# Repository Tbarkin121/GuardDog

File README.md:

# GuardDog
Makeing a hypoallergenic robot quadruped pet from scratch

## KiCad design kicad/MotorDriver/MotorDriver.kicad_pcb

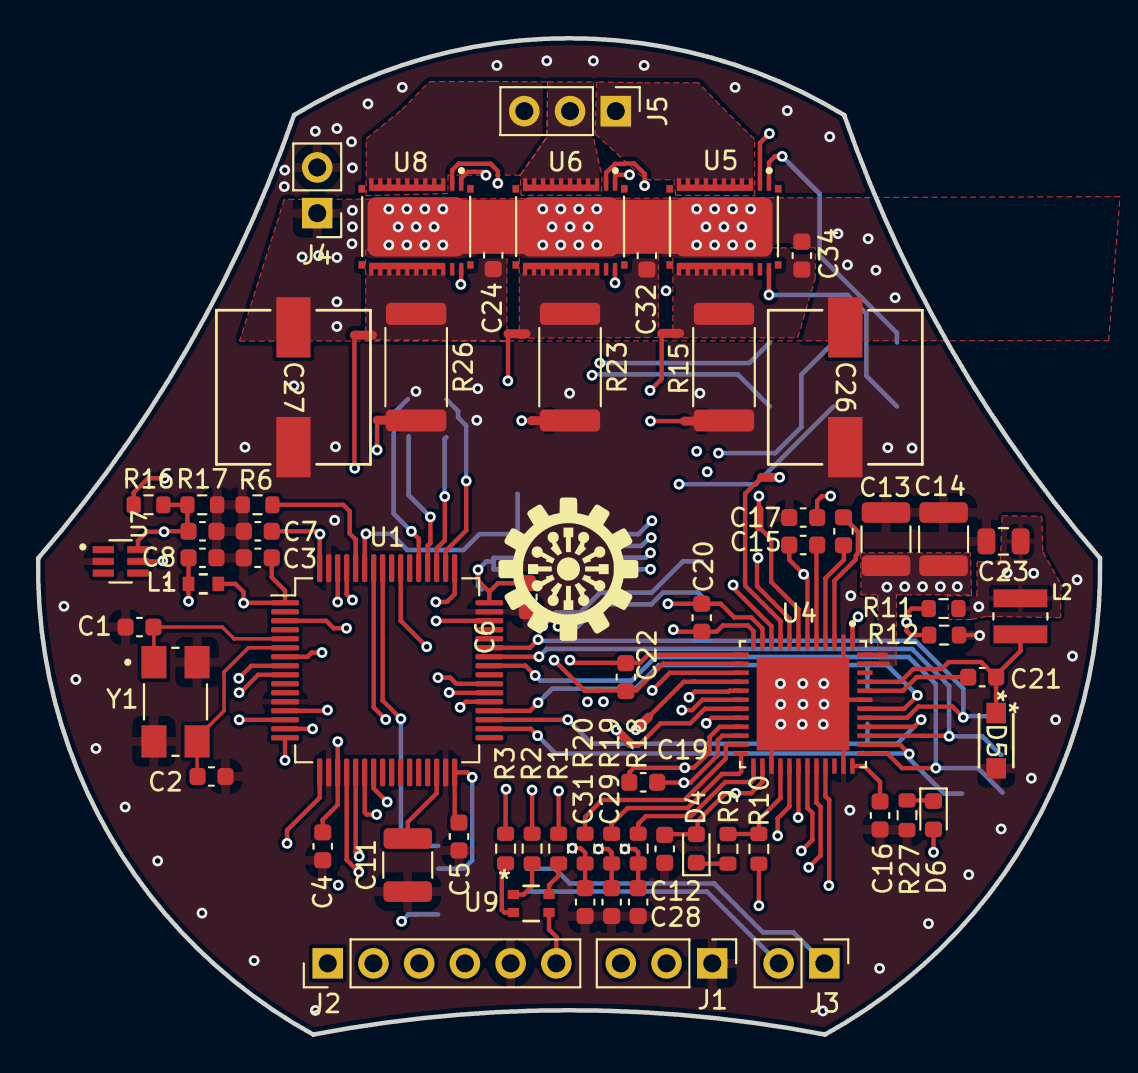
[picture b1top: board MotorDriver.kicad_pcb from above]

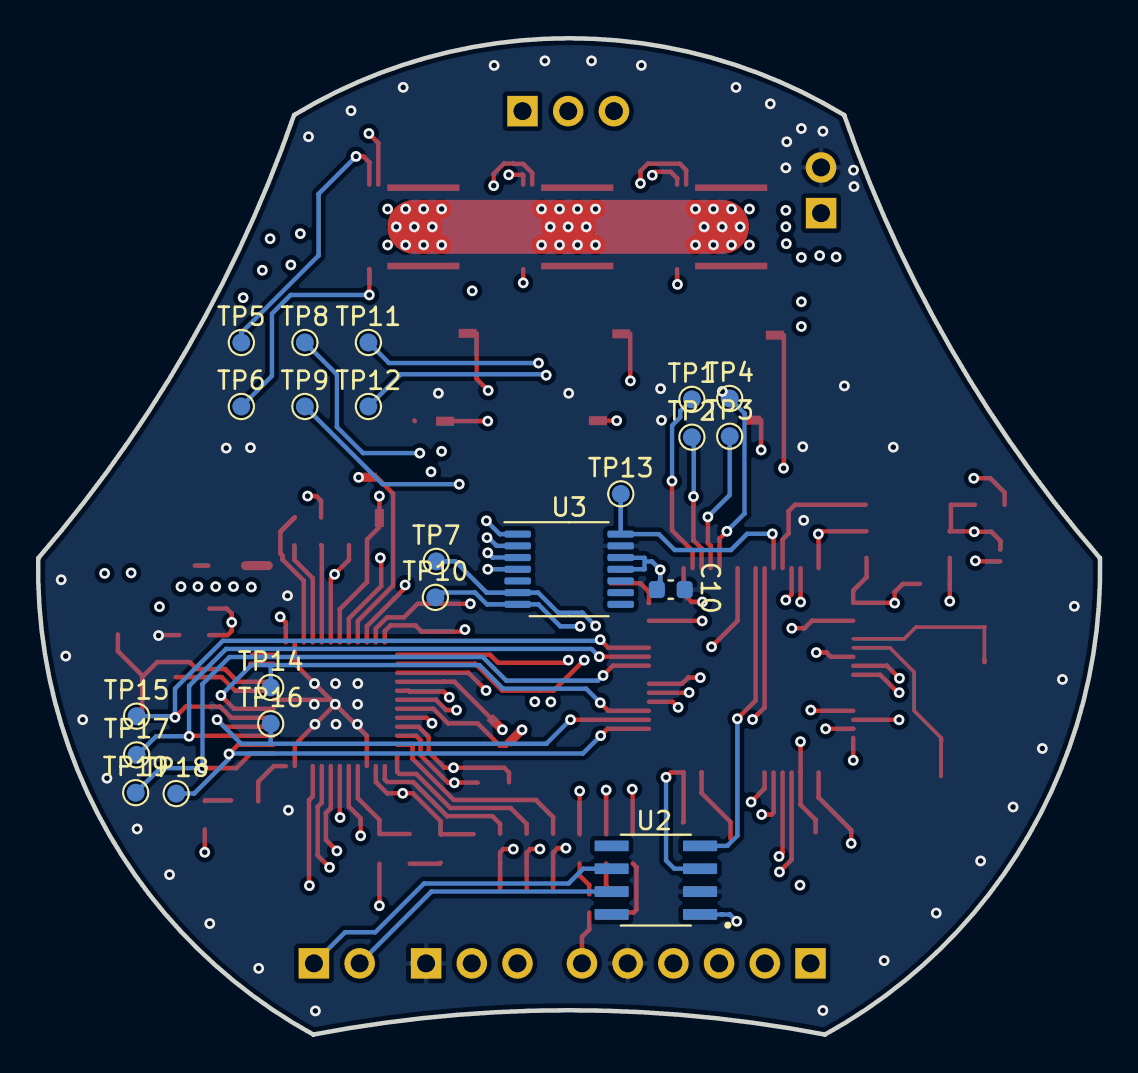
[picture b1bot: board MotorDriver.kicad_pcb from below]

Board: 4 copper layers, 59.0 x 55.3 mm, 97 parts (22 on the bottom side), 84 nets.

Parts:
C1, C2: 18pF; C_0603_1608Metric
C3, C4, C5, C6, C7, C8, C10, C12, C15, C21, C30: 0.1uF; C_0603_1608Metric
C11, C13: 4.7uF; C_1210_3225Metric
C14: 2.2uF; C_1210_3225Metric
C16, C17: 1uF; C_0603_1608Metric
C18: 0.047uF; C_0603_1608Metric
C19, C20, C22: 1000pF; C_0603_1608Metric
C23: 22uF; C_0805_2012Metric
C24, C34: 10000pF; C_0603_1608Metric
C26, C27: 220uF; CHEMI-HA0
C28, C29, C31: 2200pF; C_0603_1608Metric
C32: 10000 pF; C_0603_1608Metric
D4: RedLED; LED_0603_1608Metric
D5: NRVB1H100SFT3G; DIODE_SOD123LF_2P9X1P8_ONS
D6: BlueLED; LED_0603_1608Metric
J1: Conn_01x03_Pin; PinHeader_1x03_P2.54mm_Vertical
J2: Conn_01x06_Pin; PinHeader_1x06_P2.54mm_Vertical
J3: Conn_01x02_Pin; PinHeader_1x02_P2.54mm_Vertical
J4: Conn_01x02_Socket; PinHeader_1x02_P2.54mm_Vertical
J5: Conn_01x03_Socket; PinHeader_1x03_P2.54mm_Vertical
L1: MMZ1608B601CTAH0; IND_1608_TDK
L2: 15uH; IND_VLS3015CX-150M-1
NT1, NT2, NT3, NT4, NT5, NT6, NT7, NT8, NT9, NT10: NetTie_2; NetTie-2_SMD_Pad0.5mm
R1, R9, R27: 330; R_0603_1608Metric
R2, R3: 1k; R_0603_1608Metric
R6, R10: 10k; R_0603_1608Metric
R11: 28.0k; R_0603_1608Metric
R12: 8.45k; R_0603_1608Metric
R15, R23, R26: 0.007; R_2512_6332Metric
R16: 82.0k; R_0603_1608Metric
R17: 4.99k; R_0603_1608Metric
R18, R19, R20: 56; R_0603_1608Metric
TP1, TP2, TP3, TP4, TP5, TP6, TP7, TP8, TP9, TP10, TP11, TP12, TP13, TP14, TP15, TP16, TP17, TP18, TP19: TestPoint; TestPoint_Pad_D1.0mm
U1: STM32F446RETx; LQFP-64_10x10mm_P0.5mm
U2: ATA6560-GAQW; SOIC127P600X175-8N
U3: AS5147U; TSSOP-14_4.4x5mm_P0.65mm
U4: DRV8323RSRGZR; QFN50P700X700X100-49N
U5, U6, U8: CSD88599Q5DC; MOSFET_CSD88599Q5DC
U7: TPD4S009DCKR; SOT65P210X110-6N
U9: 150066M153000; CHIP_M153000_WRE
Y1: 406I35D08M00000; XTAL_406I35D08M00000

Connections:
+3.3V: C3.2, C4.2, C5.2, C6.2, C7.2, C10.2, C12.1, C23.1, D4.2 (A), D6.2 (A), J2.6, L1.2, L2.2, R10.1, R11.1, U1.1 (VBAT), U1.19 (VDD), U1.32 (VDD), U1.48 (VDD), U1.64 (VDD), U2.3 (VCC), U3.11 (VDD), U3.12 (3V3), U4.26 (VREF), U7.5 (VCC), U9.4
/Encoder/M1_ENC.A: TP10.1, U1.61 (PB8), U3.7 (A)
/Encoder/M1_ENC.B: TP7.1, U1.62 (PB9), U3.6 (B)
/Encoder/M1_ENC.I: TP13.1, U1.59 (PB7), U3.14 (I/PWM)
/Encoder/SPI3.CS: TP1.1, U1.50 (PA15), U3.1 (CSn)
/Encoder/SPI3.MISO: TP3.1, U1.52 (PC11), U3.3 (MISO)
/Encoder/SPI3.MOSI: TP4.1, U1.53 (PC12), U3.4 (MOSI)
/Encoder/SPI3.SCK: TP2.1, U1.51 (PC10), U3.2 (CLK)
/Microcontroller/BOOT0: R6.1, U1.60 (BOOT0)
/Microcontroller/CAN2_RX: U1.57 (PB5), U2.4 (RXD)
/Microcontroller/CAN2_TX: U1.58 (PB6), U2.1 (TXD)
/Microcontroller/CLK_N: C2.2, U1.6 (PH1), Y1.3
/Microcontroller/CLK_P: C1.2, U1.5 (PH0), Y1.1
/Microcontroller/DRV.ENABLE: U1.3 (PC14), U4.33 (ENABLE)
/Microcontroller/DRV.INHA: TP19.1, U1.41 (PA8), U4.37 (INHA)
/Microcontroller/DRV.INHB: TP17.1, U1.42 (PA9), U4.39 (INHB)
/Microcontroller/DRV.INHC: TP15.1, U1.43 (PA10), U4.41 (INHC)
/Microcontroller/DRV.INLA: TP18.1, U1.34 (PB13), U4.38 (INLA)
/Microcontroller/DRV.INLB: TP16.1, U1.35 (PB14), U4.40 (INLB)
/Microcontroller/DRV.INLC: TP14.1, U1.36 (PB15), U4.42 (INLC)
/Microcontroller/NRST: J2.1, U1.7 (NRST)
/Microcontroller/SEN.ISENA: C28.1, R18.2, U1.14 (PA0)
/Microcontroller/SEN.ISENB: C29.1, R19.2, U1.9 (PC1)
/Microcontroller/SEN.ISENC: C31.1, R20.2, U1.8 (PC0)
/Microcontroller/SEN.VSENVM: C30.1, R16.2, R17.1, U1.15 (PA1), U7.6 (D1-)
/Microcontroller/SPI1.CS: U1.20 (PA4), U4.32 (SCS_N)
/Microcontroller/SPI1.MISO: U1.22 (PA6), U4.29 (SDO)
/Microcontroller/SPI1.MOSI: U1.23 (PA7), U4.30 (SDI)
/Microcontroller/SPI1.SCK: U1.21 (PA5), U4.31 (SCLK)
/Microcontroller/SWO: J2.4, U1.55 (PB3)
/Microcontroller/TCK: J2.2, U1.49 (PA14)
/Microcontroller/TMS: J2.3, U1.46 (PA13)
/Microcontroller/UART_RX: J1.2, U1.17 (PA3)
/Microcontroller/UART_TX: J1.3, U1.16 (PA2)
/Microcontroller/VDDA: C8.2, L1.1, U1.13 (VDDA)
/MotorController/GHA: TP5.1, U4.8 (GHA), U5.1 (GH)
/MotorController/GHB: TP8.1, U4.17 (GHB), U6.1 (GH)
/MotorController/GHC: TP11.1, U4.18 (GHC), U8.1 (GH)
/MotorController/GLA: TP6.1, U4.10 (GLA), U5.22 (GL)
/MotorController/GLB: TP9.1, U4.15 (GLB), U6.22 (GL)
/MotorController/GLC: TP12.1, U4.20 (GLC), U8.22 (GL)
/MotorController/MOTA: J5.1, U5.3 (VSW), U5.4 (VSW), U5.5 (VSW), U5.6 (VSW), U5.7 (VSW), U5.8 (VSW), U5.9 (VSW), U5.10 (VSW), U5.11 (VSW)
/MotorController/MOTB: J5.2, U6.3 (VSW), U6.4 (VSW), U6.5 (VSW), U6.6 (VSW), U6.7 (VSW), U6.8 (VSW), U6.9 (VSW), U6.10 (VSW), U6.11 (VSW)
/MotorController/MOTC: J5.3, U8.3 (VSW), U8.4 (VSW), U8.5 (VSW), U8.6 (VSW), U8.7 (VSW), U8.8 (VSW), U8.9 (VSW), U8.10 (VSW), U8.11 (VSW)
/MotorController/SHA: NT3.2, U4.9 (SHA)
/MotorController/SHB: NT7.2, U4.16 (SHB)
/MotorController/SHC: NT10.2, U4.19 (SHC)
/MotorController/SLA: C24.2, NT1.2, R15.1, U5.12 (PGND), U5.13 (PGND), U5.14 (PGND), U5.15 (PGND), U5.16 (PGND), U5.17 (PGND), U5.18 (PGND), U5.19 (PGND), U5.20 (PGND)
/MotorController/SLB: C32.2, NT5.2, R23.1, U6.12 (PGND), U6.13 (PGND), U6.14 (PGND), U6.15 (PGND), U6.16 (PGND), U6.17 (PGND), U6.18 (PGND), U6.19 (PGND), U6.20 (PGND)
/MotorController/SLC: C34.2, NT8.2, R26.1, U8.12 (PGND), U8.13 (PGND), U8.14 (PGND), U8.15 (PGND), U8.16 (PGND), U8.17 (PGND), U8.18 (PGND), U8.19 (PGND), U8.20 (PGND)
/MotorController/SNA: C20.2, NT2.1, U4.12 (SNA)
/MotorController/SNB: C22.2, NT6.1, U4.13 (SNB)
/MotorController/SNC: C19.2, NT9.1, U4.22 (SNC)
/MotorController/SOA: R18.1, U4.25 (SOA)
/MotorController/SOB: R19.1, U4.24 (SOB)
/MotorController/SOC: R20.1, U4.23 (SOC)
/MotorController/SPA: C20.1, NT1.1, U4.11 (SPA)
/MotorController/SPB: C22.1, NT5.1, U4.14 (SPB)
/MotorController/SPC: C19.1, NT8.1, U4.21 (SPC)
/MotorController/VDRAIN: NT4.1, U4.7 (VDRAIN)
/MotorController/nFault: R9.2, R10.2, U4.28 (FAULT_N)
GND: C1.1, C2.1, C3.1, C4.1, C5.1, C6.1, C7.1, C8.1, C10.1, C11.1, C12.2, C13.2, C14.2, C15.2, C16.2, C23.2, C26.2, C27.2, C28.2, C29.2, C30.2, C31.2, D5.2 (A), J1.1, J2.5, J4.2, NT2.2, NT6.2, NT9.2, R6.2, R12.2, R15.2, R17.2, R23.2, R26.2, R27.2, U1.12 (VSSA), U1.18 (VSS), U1.31 (VSS), U1.47 (VSS), U1.63 (VSS), U2.2 (GND), U3.13 (GND), U4.2 (PGND), U4.27 (DGND), U4.35 (AGND), U4.43 (BGND), U4.49 (EP), U7.2 (GND), Y1.2 (GND), Y1.4 (GND__1)
unnamed: D4.1 (K), R9.1
unnamed: C21.2, D5.1 (K), L2.1, U4.45 (SW)
unnamed: D6.1 (K), R27.1
unnamed: J3.1, U2.6 (CANL)
unnamed: J3.2, U2.7 (CANH)
unnamed: R1.2, U9.3
unnamed: R2.2, U9.2
unnamed: R3.2, U9.1
unnamed: R1.1, U1.37 (PC6)
unnamed: R2.1, U1.38 (PC7)
unnamed: R3.1, U1.39 (PC8)
unnamed: C11.2, U1.30 (VCAP_1)
unnamed: C21.1, U4.44 (CB)
unnamed: C18.1, U4.4 (CPH)
unnamed: C18.2, U4.3 (CPL)
unnamed: C16.1, U4.36 (DVDD)
unnamed: R11.2, R12.1, U4.1 (FB)
unnamed: C17.2, U4.5 (VCP)
unnamed: NT3.1, U5.2 (SH)
unnamed: NT7.1, U6.2 (SH)
unnamed: NT10.1, U8.2 (SH)
Vdrive: C13.1, C14.1, C15.1, C17.1, C24.1, C26.1, C27.1, C32.1, C34.1, J4.1, NT4.2, R16.1, U4.6 (VM), U4.47 (VIN), U4.48 (SHDN_N), U5.27 (VIN), U6.27 (VIN), U8.27 (VIN)

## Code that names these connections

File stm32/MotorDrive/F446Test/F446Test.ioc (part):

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Mcu.Name=STM32F446R(C-E)Tx
Mcu.Package=LQFP64
Mcu.UserName=STM32F446RETx
PA0-WKUP.GPIOParameters=GPIO_Label
PA0-WKUP.GPIO_Label=M1_CURR_AMPL_U
PA0-WKUP.Signal=ADCx_IN0
PA1.GPIOParameters=GPIO_Label
PA1.GPIO_Label=M1_BUS_VOLTAGE
PA1.Signal=ADCx_IN1
PA10.GPIOParameters=GPIO_Speed,GPIO_PuPd,GPIO_Label
PA10.GPIO_Label=M1_PWM_WH
PA10.GPIO_PuPd=GPIO_PULLDOWN
PA10.GPIO_Speed=GPIO_SPEED_FREQ_HIGH
PA10.Signal=S_TIM1_CH3
PA13.Mode=Trace_Asynchronous_SW
PA13.Signal=SYS_JTMS-SWDIO
PA14.Mode=Trace_Asynchronous_SW
PA14.Signal=SYS_JTCK-SWCLK
PA15.GPIOParameters=GPIO_Label
PA15.GPIO_Label=SPI3_CS
PA15.Signal=GPIO_Output
PA2.GPIOParameters=GPIO_Speed,GPIO_PuPd,GPIO_Label,GPIO_Mode
PA2.GPIO_Label=UART_TX
PA2.GPIO_Mode=GPIO_MODE_AF_PP
PA2.GPIO_PuPd=GPIO_NOPULL
PA2.GPIO_Speed=GPIO_SPEED_FREQ_LOW
PA2.Mode=Asynchronous
PA2.Signal=USART2_TX
PA3.GPIOParameters=GPIO_Speed,GPIO_PuPd,GPIO_Label,GPIO_Mode
PA3.GPIO_Label=UART_RX
PA3.GPIO_Mode=GPIO_MODE_AF_PP
PA3.GPIO_PuPd=GPIO_NOPULL
PA3.GPIO_Speed=GPIO_SPEED_FREQ_LOW
PA3.Mode=Asynchronous
PA3.Signal=USART2_RX
PA4.GPIOParameters=GPIO_Label
PA4.GPIO_Label=SPI1_CS
PA4.Signal=GPIO_Output
PA5.Mode=Full_Duplex_Master
PA5.Signal=SPI1_SCK
PA6.Mode=Full_Duplex_Master
PA6.Signal=SPI1_MISO
PA7.Mode=Full_Duplex_Master
PA7.Signal=SPI1_MOSI
PA8.GPIOParameters=GPIO_Speed,GPIO_PuPd,GPIO_Label
PA8.GPIO_Label=M1_PWM_UH
PA8.GPIO_PuPd=GPIO_PULLDOWN
PA8.GPIO_Speed=GPIO_SPEED_FREQ_HIGH
PA8.Signal=S_TIM1_CH1
PA9.GPIOParameters=GPIO_Speed,GPIO_PuPd,GPIO_Label
PA9.GPIO_Label=M1_PWM_VH
PA9.GPIO_PuPd=GPIO_PULLDOWN
PA9.GPIO_Speed=GPIO_SPEED_FREQ_HIGH
PA9.Signal=S_TIM1_CH2
PB13.GPIOParameters=GPIO_Speed,GPIO_PuPd,GPIO_Label
PB13.GPIO_Label=M1_PWM_UL
PB13.GPIO_PuPd=GPIO_PULLDOWN
PB13.GPIO_Speed=GPIO_SPEED_FREQ_HIGH
PB13.Mode=PWM Generation1 CH1 CH1N
PB13.Signal=TIM1_CH1N
PB14.GPIOParameters=GPIO_Speed,GPIO_PuPd,GPIO_Label
PB14.GPIO_Label=M1_PWM_VL
PB14.GPIO_PuPd=GPIO_PULLDOWN
PB14.GPIO_Speed=GPIO_SPEED_FREQ_HIGH
PB14.Mode=PWM Generation2 CH2 CH2N
PB14.Signal=TIM1_CH2N
PB15.GPIOParameters=GPIO_Speed,GPIO_PuPd,GPIO_Label
PB15.GPIO_Label=M1_PWM_WL
PB15.GPIO_PuPd=GPIO_PULLDOWN
PB15.GPIO_Speed=GPIO_SPEED_FREQ_HIGH
PB15.Mode=PWM Generation3 CH3 CH3N
PB15.Signal=TIM1_CH3N
PB3.Mode=Trace_Asynchronous_SW
PB3.Signal=SYS_JTDO-SWO
PB5.Mode=CAN_Activate
PB5.Signal=CAN2_RX
PB6.Mode=CAN_Activate
PB6.Signal=CAN2_TX
PB8.GPIOParameters=GPIO_Label
PB8.GPIO_Label=M1_ENCODER_A
PB8.Signal=S_TIM2_CH1_ETR
PB9.GPIOParameters=GPIO_Label
PB9.GPIO_Label=M1_ENCODER_B
PB9.Signal=S_TIM2_CH2
PC0.GPIOParameters=GPIO_Label
PC0.GPIO_Label=M1_CURR_AMPL_W
PC0.Signal=ADCx_IN10
PC1.GPIOParameters=GPIO_Label
PC1.GPIO_Label=M1_CURR_AMPL_V
PC1.Signal=ADCx_IN11
PC10.Mode=Full_Duplex_Master
PC10.Signal=SPI3_SCK
PC11.Mode=Full_Duplex_Master
PC11.Signal=SPI3_MISO
PC12.Mode=Full_Duplex_Master
PC12.Signal=SPI3_MOSI
PC13.GPIOParameters=GPIO_PuPd,GPIO_Label,GPIO_ModeDefaultEXTI
PC13.GPIO_Label=Start/Stop [PushButton]
PC13.GPIO_ModeDefaultEXTI=GPIO_MODE_IT_FALLING
PC13.GPIO_PuPd=GPIO_NOPULL
PC13.Signal=GPXTI13
PC3.Signal=ADCx_IN13
PC4.Signal=ADCx_IN14
PC5.Signal=ADCx_IN15
PH0-OSC_IN.Mode=HSE-External-Oscillator
PH0-OSC_IN.Signal=RCC_OSC_IN
PH1-OSC_OUT.Mode=HSE-External-Oscillator
PH1-OSC_OUT.Signal=RCC_OSC_OUT
RCC.HSE_VALUE=8000000
RCC.SYSCLKFreq_VALUE=180000000
RCC.SYSCLKSource=RCC_SYSCLKSOURCE_PLLCLK
board=custom

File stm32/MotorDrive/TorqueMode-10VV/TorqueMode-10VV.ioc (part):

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Mcu.Name=STM32F446R(C-E)Tx
Mcu.Package=LQFP64
Mcu.UserName=STM32F446RETx
PA0-WKUP.GPIOParameters=GPIO_Label
PA0-WKUP.GPIO_Label=M1_CURR_AMPL_U
PA0-WKUP.Signal=ADCx_IN0
PA1.GPIOParameters=GPIO_Label
PA1.GPIO_Label=M1_BUS_VOLTAGE
PA1.Signal=ADCx_IN1
PA10.GPIOParameters=GPIO_Speed,GPIO_PuPd,GPIO_Label
PA10.GPIO_Label=M1_PWM_WH
PA10.GPIO_PuPd=GPIO_PULLDOWN
PA10.GPIO_Speed=GPIO_SPEED_FREQ_HIGH
PA10.Signal=S_TIM1_CH3
PA15.GPIOParameters=GPIO_Speed,GPIO_Label
PA15.GPIO_Label=SPI3_CS
PA15.GPIO_Speed=GPIO_SPEED_FREQ_VERY_HIGH
PA15.Signal=GPIO_Output
PA2.GPIOParameters=GPIO_Speed,GPIO_PuPd,GPIO_Label,GPIO_Mode
PA2.GPIO_Label=UART_TX
PA2.GPIO_Mode=GPIO_MODE_AF_PP
PA2.GPIO_PuPd=GPIO_NOPULL
PA2.GPIO_Speed=GPIO_SPEED_FREQ_LOW
PA2.Mode=Asynchronous
PA2.Signal=USART2_TX
PA3.GPIOParameters=GPIO_Speed,GPIO_PuPd,GPIO_Label,GPIO_Mode
PA3.GPIO_Label=UART_RX
PA3.GPIO_Mode=GPIO_MODE_AF_PP
PA3.GPIO_PuPd=GPIO_NOPULL
PA3.GPIO_Speed=GPIO_SPEED_FREQ_LOW
PA3.Mode=Asynchronous
PA3.Signal=USART2_RX
PA4.GPIOParameters=GPIO_Speed,GPIO_Label
PA4.GPIO_Label=SPI1_CS
PA4.GPIO_Speed=GPIO_SPEED_FREQ_VERY_HIGH
PA4.Signal=GPIO_Output
PA5.Mode=Full_Duplex_Master
PA5.Signal=SPI1_SCK
PA6.GPIOParameters=GPIO_PuPd
PA6.GPIO_PuPd=GPIO_PULLUP
PA6.Mode=Full_Duplex_Master
PA6.Signal=SPI1_MISO
PA7.Mode=Full_Duplex_Master
PA7.Signal=SPI1_MOSI
PA8.GPIOParameters=GPIO_Speed,GPIO_PuPd,GPIO_Label
PA8.GPIO_Label=M1_PWM_UH
PA8.GPIO_PuPd=GPIO_PULLDOWN
PA8.GPIO_Speed=GPIO_SPEED_FREQ_HIGH
PA8.Signal=S_TIM1_CH1
PA9.GPIOParameters=GPIO_Speed,GPIO_PuPd,GPIO_Label
PA9.GPIO_Label=M1_PWM_VH
PA9.GPIO_PuPd=GPIO_PULLDOWN
PA9.GPIO_Speed=GPIO_SPEED_FREQ_HIGH
PA9.Signal=S_TIM1_CH2
PB13.GPIOParameters=GPIO_Speed,GPIO_PuPd,GPIO_Label
PB13.GPIO_Label=M1_PWM_UL
PB13.GPIO_PuPd=GPIO_PULLDOWN
PB13.GPIO_Speed=GPIO_SPEED_FREQ_HIGH
PB13.Mode=PWM Generation1 CH1 CH1N
PB13.Signal=TIM1_CH1N
PB14.GPIOParameters=GPIO_Speed,GPIO_PuPd,GPIO_Label
PB14.GPIO_Label=M1_PWM_VL
PB14.GPIO_PuPd=GPIO_PULLDOWN
PB14.GPIO_Speed=GPIO_SPEED_FREQ_HIGH
PB14.Mode=PWM Generation2 CH2 CH2N
PB14.Signal=TIM1_CH2N
PB15.GPIOParameters=GPIO_Speed,GPIO_PuPd,GPIO_Label
PB15.GPIO_Label=M1_PWM_WL
PB15.GPIO_PuPd=GPIO_PULLDOWN
PB15.GPIO_Speed=GPIO_SPEED_FREQ_HIGH
PB15.Mode=PWM Generation3 CH3 CH3N
PB15.Signal=TIM1_CH3N
PB8.GPIOParameters=GPIO_Label
PB8.GPIO_Label=M1_ENCODER_A
PB8.Signal=S_TIM2_CH1_ETR
PB9.GPIOParameters=GPIO_Label
PB9.GPIO_Label=M1_ENCODER_B
PB9.Signal=S_TIM2_CH2
PC0.GPIOParameters=GPIO_Label
PC0.GPIO_Label=M1_CURR_AMPL_W
PC0.Signal=ADCx_IN10
PC1.GPIOParameters=GPIO_Label
PC1.GPIO_Label=M1_CURR_AMPL_V
PC1.Signal=ADCx_IN11
PC10.Mode=Full_Duplex_Master
PC10.Signal=SPI3_SCK
PC11.GPIOParameters=GPIO_PuPd
PC11.GPIO_PuPd=GPIO_PULLUP
PC11.Mode=Full_Duplex_Master
PC11.Signal=SPI3_MISO
PC12.Mode=Full_Duplex_Master
PC12.Signal=SPI3_MOSI
PC14-OSC32_IN.Signal=GPIO_Output
PC6.Signal=GPIO_Output
PC7.Signal=GPIO_Output
PC8.Signal=GPIO_Output
PH0-OSC_IN.Mode=HSE-External-Oscillator
PH0-OSC_IN.Signal=RCC_OSC_IN
PH1-OSC_OUT.Mode=HSE-External-Oscillator
PH1-OSC_OUT.Signal=RCC_OSC_OUT
RCC.HSE_VALUE=8000000
RCC.SYSCLKFreq_VALUE=180000000
RCC.SYSCLKSource=RCC_SYSCLKSOURCE_PLLCLK
board=custom

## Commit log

2023-11-20 Pushing project files for remote work
2023-11-27 Good progress on the leg prototype. Looking at the jacobian project again, i think I can use some stuff from that project to help size the link lengths and also something to relate the tip forces to 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
2023-11-28 Added urdf for Torque Pole
2023-11-29 Jacobians and pendulum simulation with lagrangian mechanics added
2023-11-29 Added friction and input torque. Did a constant velocity following experiment. Gonna move to multi-joint now... I think this is too simple
2023-11-29 Multisegment is in but I'm not accounting for translational energy, coriolis or centrifugal forces... needs work
2023-11-30 Still working it out...
2023-11-30 The 2 joint force / torque kinematic jacobian looks like its working.
2023-11-30 Just playing with it a bit more. It is starting to become more intuitive
2023-12-02 Just syncing from my macbook
2023-12-04 Schematic capture is like 80% complete. There are some components that don't have appropriate footprints, IE the 330 mH caps. Started board layout. I'm not sure if I can fit everything in the current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
2023-12-05 Pushing before the drive to Boston...
2023-12-12 Updated the planetary gearbox design. It is much better with retaining rings and bearing support. 95% done with the PCB routing. Need to just do a final routing check and i think I can put the order 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
2023-12-13 PCB ordered
2023-12-13 Added a new URDF with 0.5m long connections and a 500g foot piece
2023-12-13 Added some isaac stuff. Started testing the URDF in some simple python code
2023-12-20 Started to test the large bearing build
2024-01-03 Made a new torquepole assembly
2024-01-03 Created a test environment for the new URDF. I want to modify it to add a weight to the end before moving forward
2024-01-03 Added weight to the torque pole
2024-01-03 Second attempt...
2024-01-04 Kind of working, need redefine pendulum neutral state as up though
2024-01-04 Flipped the pole orientation to upward
2024-01-04 Training is working
2024-01-04 Was able to generate an onnx file from the trained pendulum model. Needed to make a modification to rl_games:torch_runner to generate the onnx file during the test playback... trying hardware in the 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
2024-01-04 Got Python to STM32 serial comms up
2024-01-06 Python script is communicating with the STM32. Python script can send two floats for the observation and recieves 4 floats (Value, Mu, Log_STD, InferenceTime). Inference time results in about a 700 H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
2024-01-06 Hardware in the loop control is working from the STM32G431. But can it run anymal terrain?
2024-01-07 Well it can't run anymal terrain due to flash size limitations. But I started looking into external memory so maybe in the future. Anymal (not terrain) runs at 96 Hz though which is pretty impressive
2024-01-14 Got most of the STM32 code together for the inverted pendulum. I just need to double check that the encoder measurements are using the same conventions as isaac
2024-01-15 The NN + Motor driver worked beautifully. Ready for the writeup. Updated URDF again, was thinking of trying some parameter randomization for a more robust policy.
2024-01-15 Updated URDF with the measured mass of the CF-tube and ASA-weight
2024-01-15 Learned a new policy with the current hardware setup, time to test on HW
2024-01-16 Got a better pendulum policy to test on HW
2024-01-16 New policy
2024-01-16 One more try for tonight
2024-01-16 Just noticed I was working out of the old LegDay directory so my changes weren't being pushed... fixed. use the cube_workspace in the future
2024-01-16 Made some models for slightly higher max torques. Also missing some MCsdk files so i cant build the embedded code on linux yet
2024-01-16 Got the stm32 directory organized. There is now one project, LegDay, which contains the torquepole code. I included the missing files that linux might not have been downloading but im not 100% sure i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
2024-02-27 Added some mecanical updates... also this project needs some file organization...
2024-03-11 Solidworks file cleanup... it was a mess!
2024-03-12 Added URDF for jump test
2024-03-12 Got keyboard control of jumpy working.
2024-03-13 Jumpy policy is working
2024-03-13 Reward function improved. Reward is now set to zero when touching the ground. Reward per time step when off the ground is the max achieved height since the foot left the ground. This promote high jum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
2024-03-15 Added Quad urdf file
2024-03-15 Updated Quad urdf
2024-03-15 Still trying to get the urdf to work, it might be coordinate system references in sub assemblies messing things up...
2024-03-15 Did redoing all the reference axis and coords help?
2024-03-16 urdf should be good this time... so close
2024-03-16 this time for sure!
2024-03-17 Added a URDF that has limited range for the hip joint
2024-03-18 added a urdf with the foot seperated into its own joint
2024-03-18 Adding training code for quad jump. training is not working well yet and needs some tweaking
2024-03-19 There is some reset bug in quad jumpy still
2024-03-20 Fixed the env reset bug. It learns better but i think the reward or observation need to be improved still.
2024-03-21 Its working pretty good for the jumpy reward test
2024-03-29 Quad Walk Policy is working ok. I think i get better finally policies with goal oriented training as oppose to input oriented training... back to waypoints!
2024-04-01 Trying shorter legs and fixed the coordinate system for Z up
2024-04-02 Walking is working ok, Coordinate fix is in along with 200mm leg connections
2024-04-03 Working on the port to Isaac Sim. So far I just got the urdf port and pulled into a new task. A lot of work to do to finish this off
2024-04-05 Found and fixed a bug with the command rerolling mid episode. All environments were getting set to the same command
2024-04-05 Modeled the guarddog environment on anymal. Training seems to be working. I still need to spend some more time porting over some of the OG code for a better comparison between the two
2024-04-10 Added an experimental Biped with reaction wheels
2024-04-10 Fixed the biped URDF after checking with isaac sim
2024-04-29 test
2024-04-30 Added a slightly adjusted biped urdf
2024-05-07 Fixed bad rotation axis from Biped_Adjust, renamed Biped_CenterHip
2024-05-08 Updated the biped foot to have a sphere instead of a cylinder. Should be more consistant contact with the ground.
2024-05-08 Got a good walking policy after an all night training. Starting to add some more rewards from the anymal terrain code. Added collision and joint accel penelty but training seems to have either slowed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
2024-05-08 Adding a no reaction wheel URDF
2024-05-19 Working on some of the solidworks model, new urdf, working on the motor drive board a little
2024-05-23 Made the hip joint more physically realistic. 3d printed it and added a new URDF to test
2024-06-20 Adding STM32 Motor Drive Stuff for testing
2024-07-02 Got the python to STM32 interface working decently. Needs some more polish but we are getting close to being able to execute NN control code
2024-07-17 Added some URDF files for the jump rigs. Also the motorcontrol sdk files for different control modes. And whatever python files I've been messing with...
2024-07-18 Set the JumpRig training environment up... time to learn
2024-07-18 Working on some wonky collision physics. I think i need to make the foot a fixed joint so it can have its own collision mesh...
2024-07-18 Updated the jump rig 2 urdf to have a seperate collision mesh for the foot element
2024-07-18 Added another collision mesh for the shin... still working out the wonky physics... it seems to be related to an self interaction of collision mesh potentially
2024-08-05 Adding some work that hasnt been pushed. Organization of the Motor Drive projects and some of the cycloidal drive experiment files
